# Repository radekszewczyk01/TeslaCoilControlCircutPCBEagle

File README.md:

### Conversion of an audio signal to control a Tesla coil using operational amplifiers

The goal of the project is to design an electronic circuit schematic in the EAGLE software that enables the conversion of an audio signal from a computer into a control signal for a Tesla coil. The project involves selecting appropriate operational amplifiers and other electronic components and integrating them into a schematic capable of processing the audio signal into a signal with the proper amplitude and frequency to control the Tesla coil.

### Acknowledgements

Special thanks to the creator of the circuit, Electroboom. You can find the circuit on his website at https://www.electroboom.com/?p=575.

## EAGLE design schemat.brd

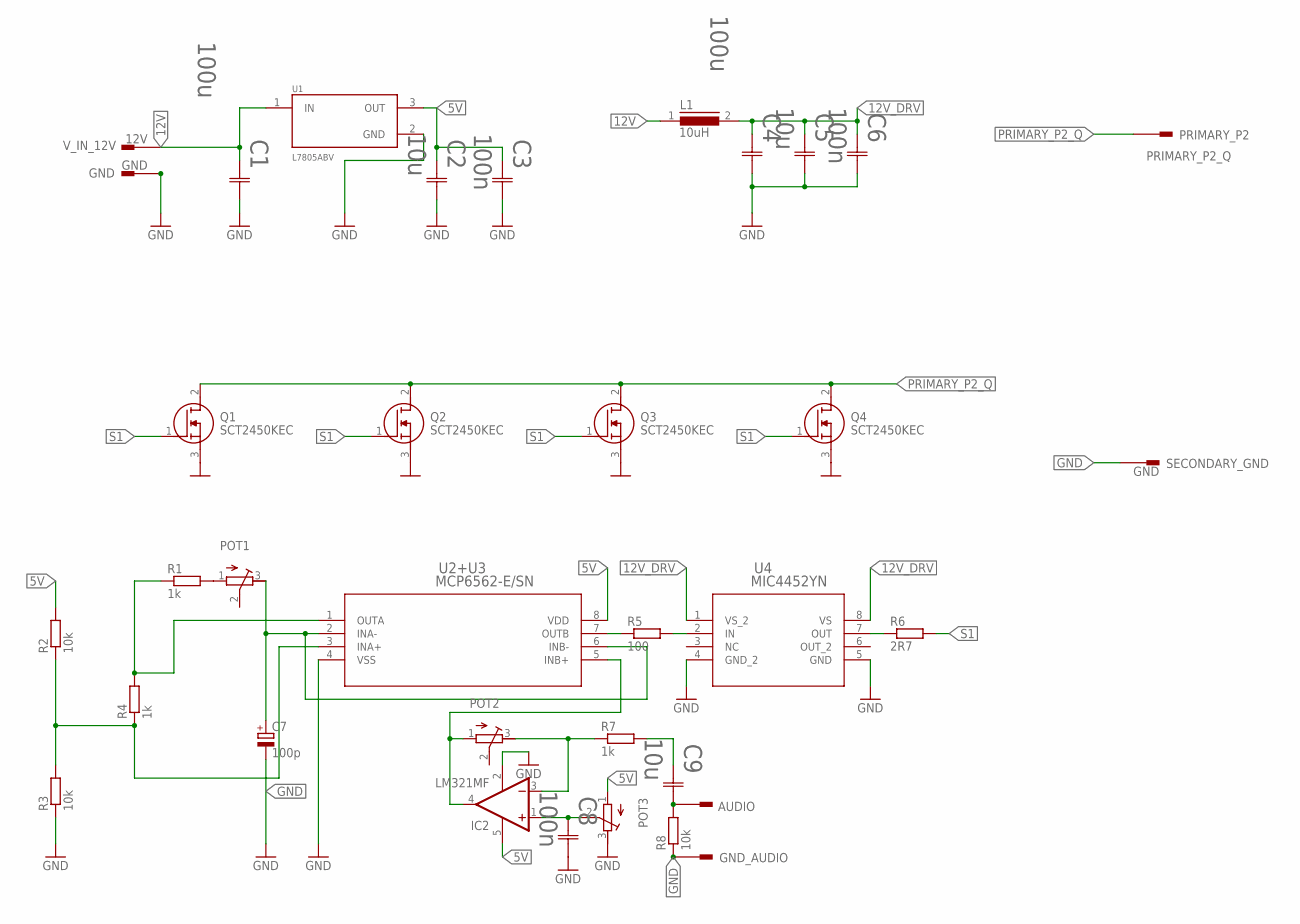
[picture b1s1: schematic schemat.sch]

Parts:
AUDIO: PIN1-2; 62221
C1, C4: 100u; CAP_YX_6P3X11_RUB
C2, C5, C9: 10u; CAP_5_X_5_PAN
C3, C6, C8: 100n; CAP_0402_WAL
C7: 100p; E1,8-4
GND: GND; 62221
GND_AUDIO: GND; 62221
IC2: LM321MF; SOT23-5
L1: 10uH; RKE4
POT1, POT2, POT3: R-TRIMM64W; RTRIM64W
PRIMARY_P2: PRIMARY_P2_Q; 62221
Q1, Q2, Q3, Q4: SCT2450KEC; TO545P521X1594X2583-3P
R1, R4, R7: 1k; 0204/7
R2, R3, R8: 10k; 0204/7
R5: 100; 0204/7
R6: 2R7; 0204/7
SECONDARY_GND: GND; 62221
U1: L7805ABV; TO254P460X1020X1945-3P
U2+U3: MCP6562-E/SN; SOIC8-N_MC_MCH
U4: MIC4452YN; PDIP8(N)_MCH
V_IN_12V: 12V; 62221

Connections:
5V: C2.1, C3.1, IC2.5 (V+), POT3.1 (A), R2.2, U1.3 (OUT), U2+U3.8 (VDD)
12V: C1.1, L1.1, U1.1 (IN), V_IN_12V.1
12V_DRV: C4.1, C5.1, C6.1, L1.2, U4.1 (VS_2), U4.8 (VS)
12V_DRV1: C8.1, IC2.1 (+IN), POT3.2 (S)
GND: C1.2, C2.2, C3.2, C4.2, C5.2, C6.2, C7.-, C8.2, GND.1, GND_AUDIO.1, IC2.2 (V-), POT3.3 (E), Q1.3 (S), Q2.3 (S), Q3.3 (S), Q4.3 (S), R3.1, R8.1, SECONDARY_GND.1, U1.2 (GND), U2+U3.4 (VSS), U4.4 (GND_2), U4.5 (GND)
unnamed: R2.1, R3.2, R4.1, U2+U3.3 (INA+)
unnamed: R1.1, R4.2, U2+U3.1 (OUTA)
unnamed: POT1.1 (A), R1.2
unnamed: C7.+, POT1.3 (E), U2+U3.2 (INA-), U2+U3.6 (INB-)
unnamed: R5.1, U2+U3.7 (OUTB)
unnamed: R5.2, U4.2 (IN)
unnamed: R6.1, U4.7 (OUT)
unnamed: IC2.4 (OUT), POT2.1 (A), U2+U3.5 (INB+)
unnamed: C9.1, R7.2
unnamed: IC2.3 (-IN), POT2.3 (E), R7.1
unnamed: AUDIO.1, C9.2, R8.2
PRIMARY_P2_Q: PRIMARY_P2.1, Q1.2 (D), Q2.2 (D), Q3.2 (D), Q4.2 (D)
S1: Q1.1 (G), Q2.1 (G), Q3.1 (G), Q4.1 (G), R6.2

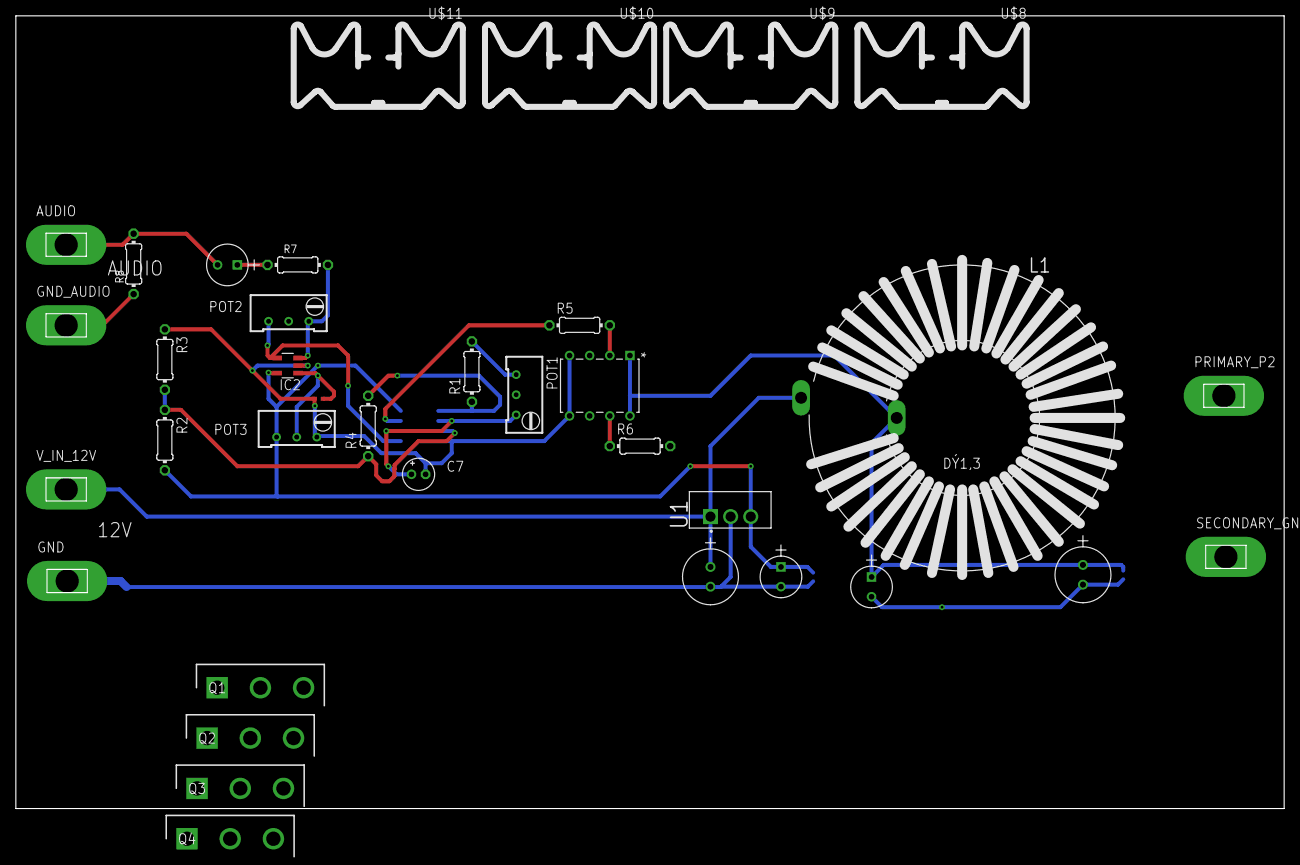
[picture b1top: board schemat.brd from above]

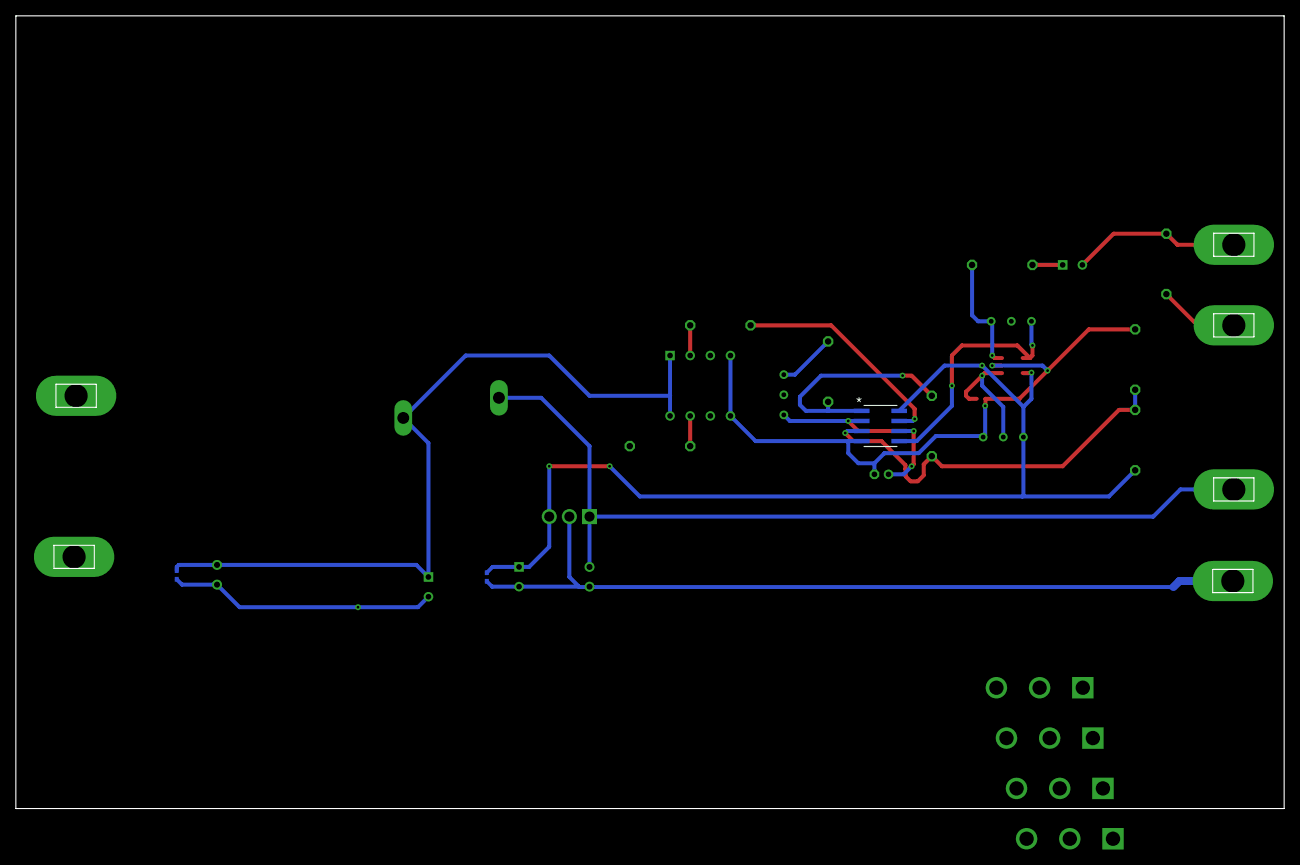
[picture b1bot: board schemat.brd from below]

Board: 2 copper layers, 160.0 x 100.0 mm, 39 parts (3 on the bottom side), 18 nets.

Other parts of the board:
U$8, U$9, U$10, U$11: PF752

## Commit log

2024-08-07 start
2024-08-12 main units
2024-08-12 description
2024-08-12 schematic ready
2024-08-14 project finished
2025-01-13 transistor changed

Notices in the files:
parts and their libraries:
MCP6562-E_SN: COPYRIGHT: Copyright (C) 2024 Ultra Librarian. All rights reserved.
